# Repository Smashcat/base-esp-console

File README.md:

# base-esp-console
The original ESP console, without USB programming circuit. Includes code for Tetris game, and nodejs game server :)

esp_tetris directory contains the multi-player Tetris game that can be built in the Arduino IDE

arduino_libs directory contains a couple of customised libraries required by Arduino IDE to build the project

gameserver.zip contains the nodejs socket server that allows multi-player. You do not need this for single player

Video of console working: https://www.youtube.com/watch?v=wQm9_M8K_SY&t=9s (older version of game)

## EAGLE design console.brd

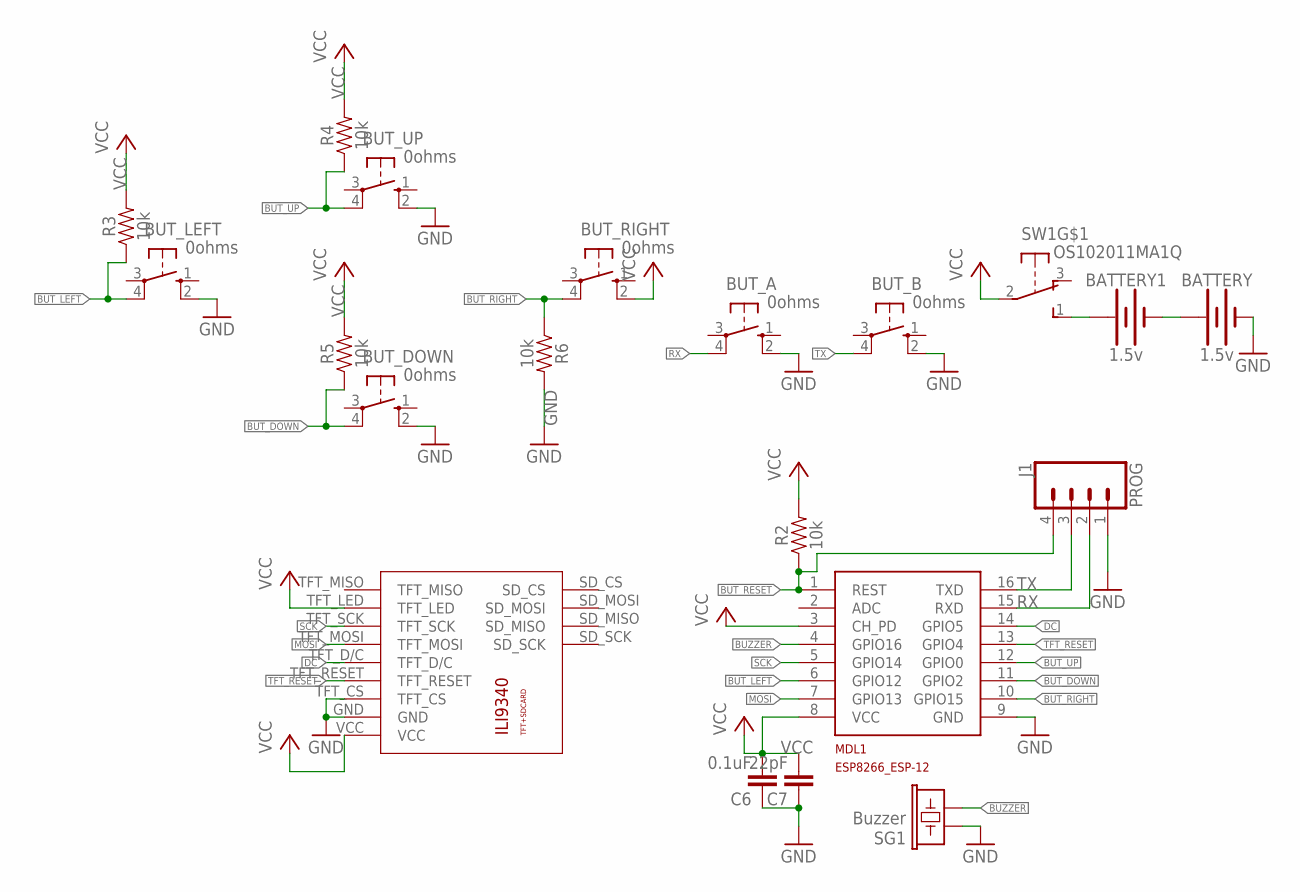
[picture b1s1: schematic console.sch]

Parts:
BATTERY, BATTERY1: 1.5v; BATTERY-AA
BUT_A: 0ohms; B3F-10XX
BUT_B: 0ohms; B3F-10XX
BUT_DOWN: 0ohms; B3F-10XX
BUT_LEFT: 0ohms; B3F-10XX
BUT_RIGHT: 0ohms; B3F-10XX
BUT_UP: 0ohms; B3F-10XX
C6: 0.1uF; C0603
C7: 22pF; C0603
J1: PROG; 1X04_NO_SILK
MDL1: MCU; ESP8266-ESP12
R2, R3, R4, R5, R6: 10k; 0603
SG1: Buzzer; BUZZER-CCV
SW1: OS102011MA1Q
U$1: ILI9340

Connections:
BATT+: BATTERY1.PWR@1 (+), SW1.1 (S)
BATT_LINK: BATTERY.PWR@1 (+), BATTERY1.GND@1 (-)
BUT_DOWN: BUT_DOWN.4 (P1), MDL1.11 (GPIO2), R5.1
BUT_LEFT: BUT_LEFT.4 (P1), MDL1.6 (GPIO12), R3.1
BUT_RESET: J1.4, MDL1.1 (REST), R2.1
BUT_RIGHT: BUT_RIGHT.4 (P1), MDL1.10 (GPIO15), R6.1
BUT_UP: BUT_UP.4 (P1), MDL1.12 (GPIO0), R4.1
BUZZER: MDL1.4 (GPIO16), SG1.- (2)
DC: MDL1.14 (GPIO5), U$1.TFT_D/C
GND: BATTERY.GND@1 (-), BUT_A.2 (S1), BUT_B.2 (S1), BUT_DOWN.2 (S1), BUT_LEFT.2 (S1), BUT_UP.2 (S1), C6.1, C7.1, J1.1, MDL1.9 (GND), R6.2, SG1.+ (1), U$1.GND, U$1.TFT_CS
MOSI: MDL1.7 (GPIO13), U$1.TFT_MOSI
RX: BUT_A.4 (P1), J1.2, MDL1.15 (RXD)
SCK: MDL1.5 (GPIO14), U$1.TFT_SCK
TFT_RESET: MDL1.13 (GPIO4), U$1.TFT_RESET
TX: BUT_B.4 (P1), J1.3, MDL1.16 (TXD)
VCC: BUT_RIGHT.2 (S1), C6.2, C7.2, MDL1.3 (CH_PD), MDL1.8 (VCC), R2.2, R3.2, R4.2, R5.2, SW1.2, U$1.TFT_LED, U$1.VCC

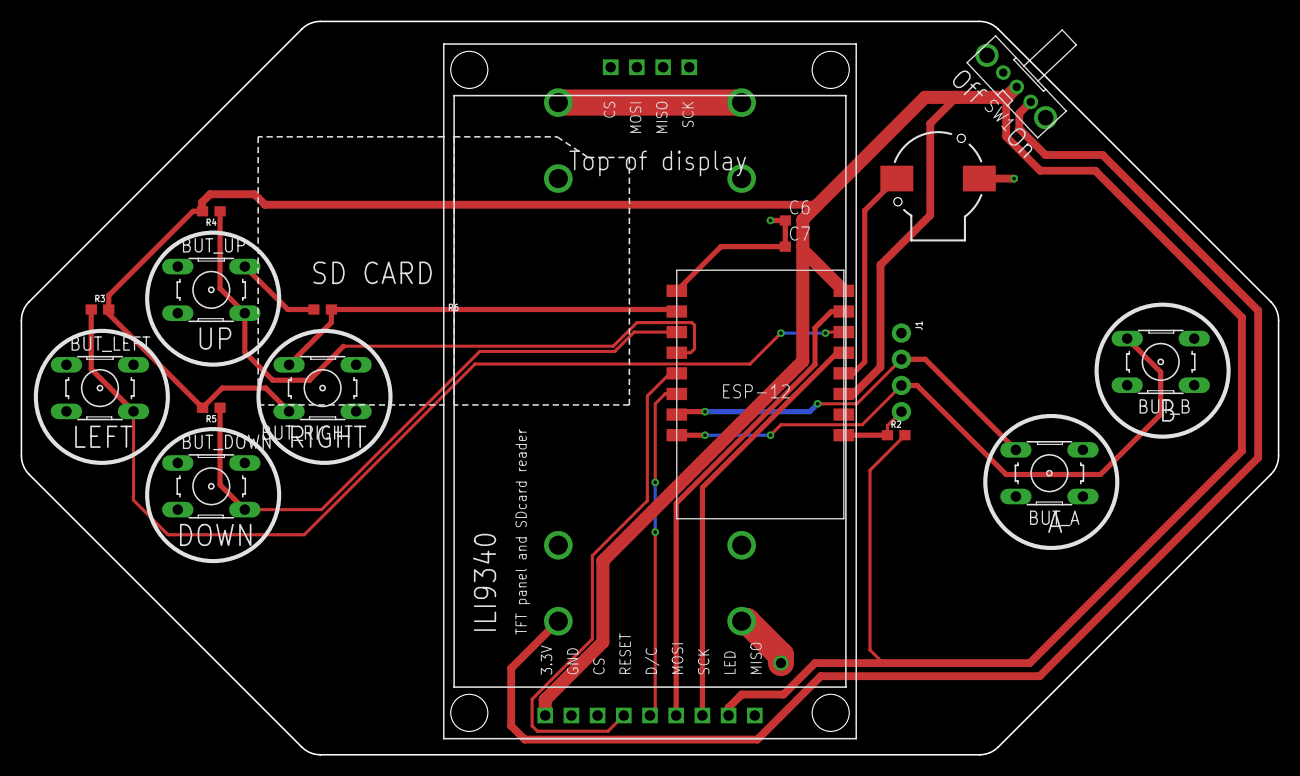
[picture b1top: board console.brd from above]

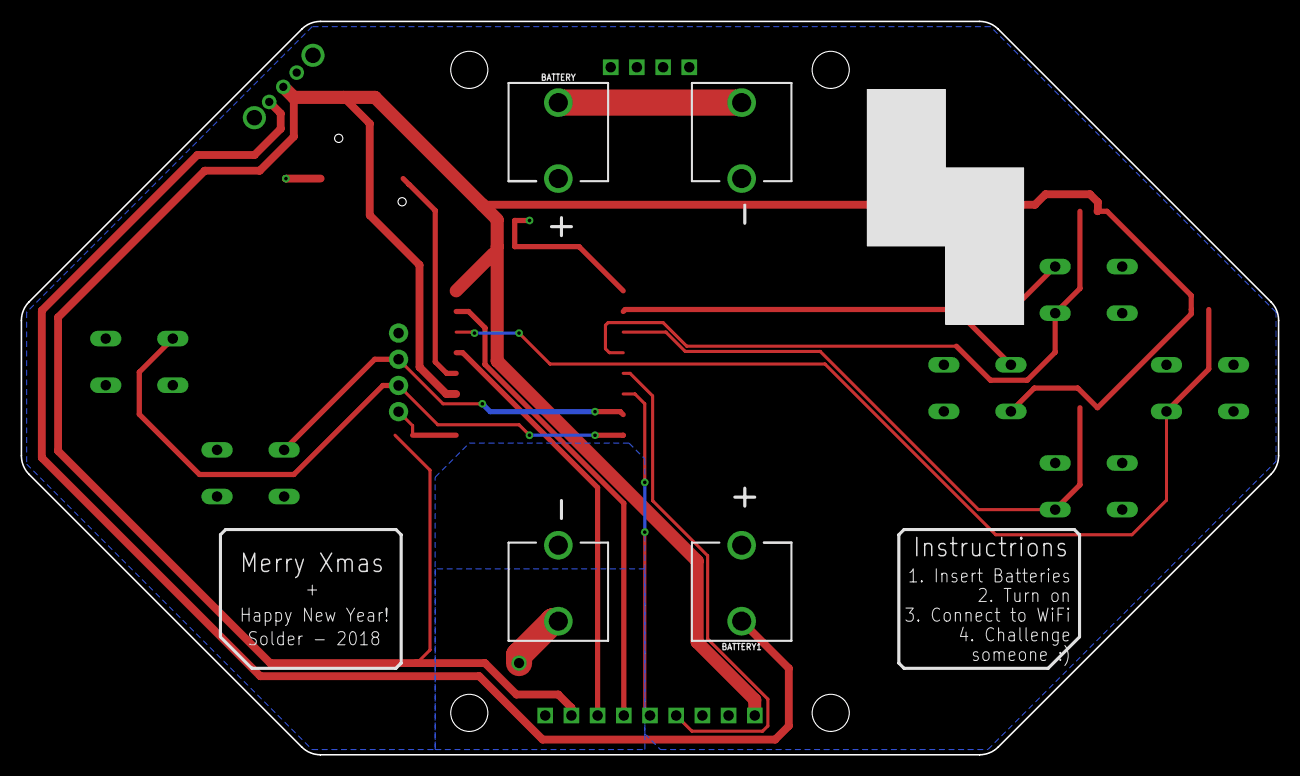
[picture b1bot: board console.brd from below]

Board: 2 copper layers, 121.9 x 71.1 mm, 20 parts (2 on the bottom side), 16 nets.

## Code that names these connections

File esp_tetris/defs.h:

// true if using the dev version of the console - button mappings are different
#define DEV_VERSION       false

// True if using dev server for networking comms (addresses below)
#define DEV_SERVER        false

// True if serial port should output debugging data. Cannot be used in conjunction with A+B buttons
#define USE_SERIAL        false

// Leave following set to false - code is not finished!
#define NEW_NETWORK       false

// Number of starts in background of out-of-game screens
#define NSTARS            512


// There should be no need to alter anything below this line!

// Ping server once a minute
#define PING_INTERVAL     6000

#define TMP_STR_LEN       500

#if DEV_SERVER
#define GAME_SERVER_URL   "192.168.0.249"
#else
#define GAME_SERVER_URL   "www.your-domain.com"
#endif

#define GAME_SERVER_PORT  9999
#define MAX_OPPONENTS     30
#define APP_SIG0          101
#define APP_SIG1          102

#define BUT_UP     0
#define BUT_RLEFT  1
#define BUT_DOWN   2
#define BUT_RRIGHT 3
#if(DEV_VERSION)
#define BUT_LEFT 4
#else
#define BUT_LEFT  12
#endif
#define TFT_RST    4
#define DC         5
#define MISO      12
#define MOSI      13
#define SCLK      14
#define BUT_RIGHT 15
#define BUZZER    16

// program states
#define STATE_INTRO         0
#define STATE_TITLE_SCREEN  1
#define STATE_HIGH_SCORES   2
#define STATE_SETTINGS      3
#define STATE_HELP          4
#define STATE_SETUP_NAME    5
#define STATE_SETUP_WIFI    6
#define STATE_SETUP_ABOUT   7

// In game
#define STATE_CHALLENGED      70
#define STATE_PICK_PLAYER     80
#define STATE_GAME_START      90
#define STATE_PLAYING         100
#define STATE_CHOOSE_OPPONENT 110
#define STATE_GAME_END        120

#define RED_TO_YELLOW   0
#define GREEN_TO_BLUE   1
#define PURPLE_TO_WHITE 2
#define WHITE_TO_BLUE   3
#define RED_TO_BLUE     4
#define BLACK_TO_RED    5
#define BLACK_TO_BLACK  6

#define KS_IDLE         0
#define KS_OPENING      1
#define KS_EDITING      2
#define KS_CLOSING      3

// Actually 7 displayed shapes, but first is blank - makes some other logic easier :)
#define TOTAL_SHAPES      8
#define TOTAL_ROTATIONS   4
#define TOTAL_COORDINATES 4

#define KEYBOARD_ACTIVE 0
#define KEYBOARD_CLOSED 1
#define KEYBOARD_SAVED  2

#define GRID_X            16
#define GRID_Y            33
#define GRID_HEIGHT       23
#define GRID_WIDTH        10
#define FIRST_VISIBLE_ROW 3

// Speed of game at start (interval in 1/20 seconds between successive downward movements of player's block)
#define GAME_SPEED_START  30
// Maximum speed of game (as above)
#define GAME_SPEED_END    1
#define REPEAT_SPEED_RESET    20;
#define REPEAT_SPEED_REPEAT   2;


#define MY_NAME_IX      3
#define MY_NAME_LEN     17

#define WIFI_SSID_IX    20
#define WIFI_SSID_LEN   65

#define WIFI_PASS_IX    85
#define WIFI_PASS_LEN   65

#define SOUND_TYPE_IX   151

#define NETWORK_OFF         0
#define NETWORK_CONNECTING  1
#define NETWORK_CONNECTED   2
#define NETWORK_OFFLINE     3
#define NETWORK_UNDEFINED   4
#define WIFI_LOGO_DISPLAY_TIME  500
// 20 = 1 second
#define CONNECT_CHECK_INTERVAL  100
#define CURSOR_BLINK_SPEED      80

#define COLOR_GREY  0x421
#define COLOR_RED   0x78
#define COLOR_GREEN 0xE003
#define COLOR_BLUE  0x0F00

#define GAMESTATE_DROPPING  0
#define GAMESTATE_DROPPED   1
#define GAMESTATE_FAST_DROP 2
#define GAMESTATE_CLEARING  3
#define GAMESTATE_GAME_OVER 4
#define GAMESTATE_WE_WIN    5
#define GAMESTATE_WE_LOSE   6

#define RESPONSE_NONE       0
#define RESPONSE_ACCEPT     1
#define RESPONSE_REJECT     2
#define RESPONSE_BUSY       3

#define SOUND_NONE          0
#define SOUND_EFFECTS       1
#define SOUND_ALL           2

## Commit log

2018-12-30 Added Arduino libs that are slightly modified for game
2018-12-30 Adde nodejs gameserver
2018-12-30 Added nodejs archive
2018-12-30 Changes to defs

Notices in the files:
parts and their libraries:
SparkFun-Batteries: Licensing: Creative Commons ShareAlike 4.0 International - https://creativecommons.org/licenses/by-sa/4.0
